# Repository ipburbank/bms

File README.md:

# bms
Open source, active-balanced BMS

# Project Structure
Based on https://medium.com/inventhub/better-manage-kicad-projects-using-git-8d06e1310af8

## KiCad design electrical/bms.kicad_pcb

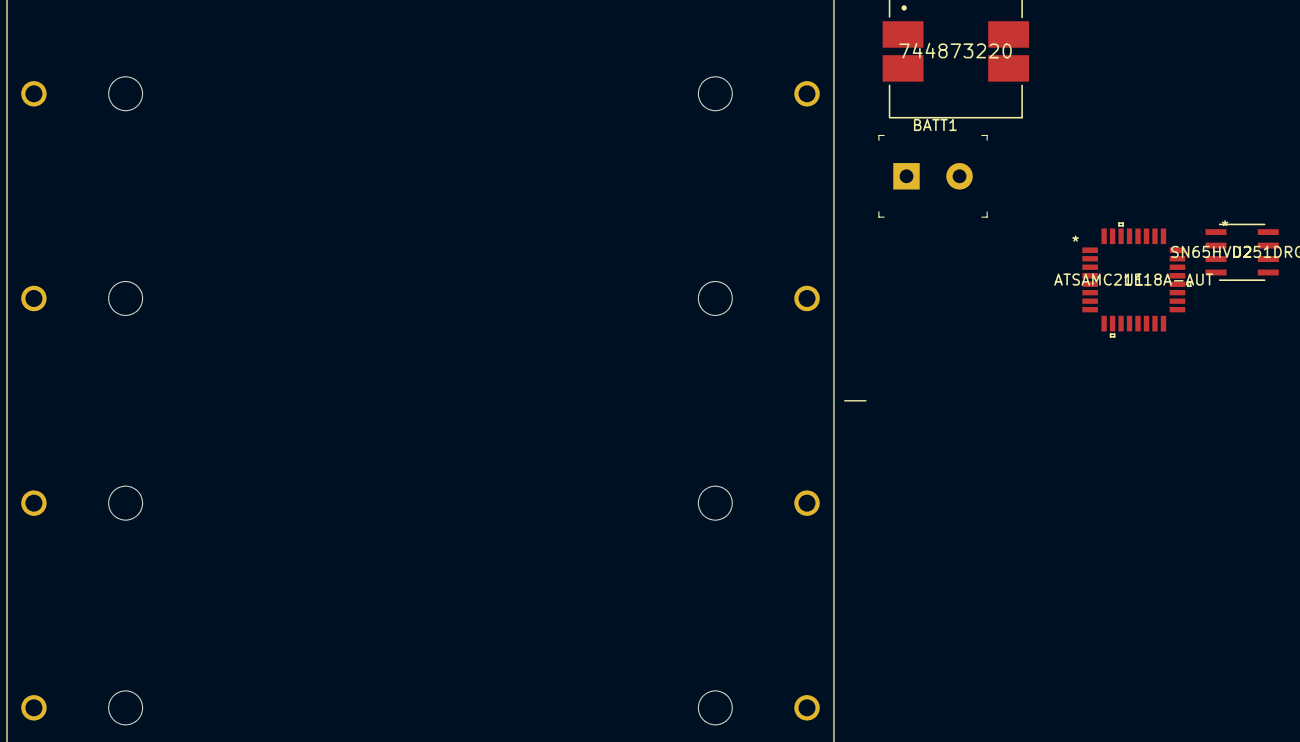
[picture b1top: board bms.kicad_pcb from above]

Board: 2 copper layers, 5 parts (0 on the bottom side), 5 nets, no tracks yet.

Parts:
BATT1: OSTTC020162; Term_Block_1x2_P5mm
BT1: BK-18650-PC8; BAT_BK-18650-PC8
L3: 744873220; Wurth_Electronics-744873220-Manufacturer_Recommended
U1: ATSAMC21E18A-AUT
U2: SN65HVD251DRG4

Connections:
+BATT: BATT1.1, BT1.1+
-BATT: BATT1.2, BT1.4, U1.10, U1.28
unnamed: BT1.1, BT1.2+, L3.3
unnamed: BT1.2, BT1.3+
unnamed: BT1.3, BT1.4+, L3.1

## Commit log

2020-07-27 Initial readme, folder struction, and blank KiCAD project
2020-08-02 4 Cell active balancing circuit
2020-08-02 Moved batteries to own sheet
2020-08-02 move digikey library to submodule

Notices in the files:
parts and their libraries:
Copyright 2016 Accelerated Designs. All rights reserved.
